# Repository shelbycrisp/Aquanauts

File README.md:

# Aquanauts
## Summary

The Exxon Valdez oil spill of 1989 is generally considered to have the largest environmental impact of any oil spill to date. Ocean Scientists at Prince William Sound have been using an underwater profiler to monitor environmental factors. The platform has an anchor that holds it at a specified depth. The platform goes to the surface of the water once a day to transmit a signal that it is still alive. The data collected on ocean life and ocean currents is not transmitted and must be retrieved by scientists. The collected data gives scientists information on how the location and its inhabitants are recovering. There are multiple ways this platform can be improved and updated. Currently, someone must retrieve the platform every few weeks in order to charge the battery and extract data. Over time the battery life has decreased, further increasing the maintenance required. If this maintenance could be decreased that would be a great improvement for the platform. Currently, it is very difficult and expensive to replace the battery. A battery that can be serviced by the scientists themselves would be ideal. The platform has many sensors on board to detect ocean life such as plankton. The current solution to classifying plankton is through the use of machine learning. However, there is room for improvement in this component. There is a weather buoy nearby that could potentially be used to install components on for communication with the platform. Our team is identifying which features/issues to focus our project on.

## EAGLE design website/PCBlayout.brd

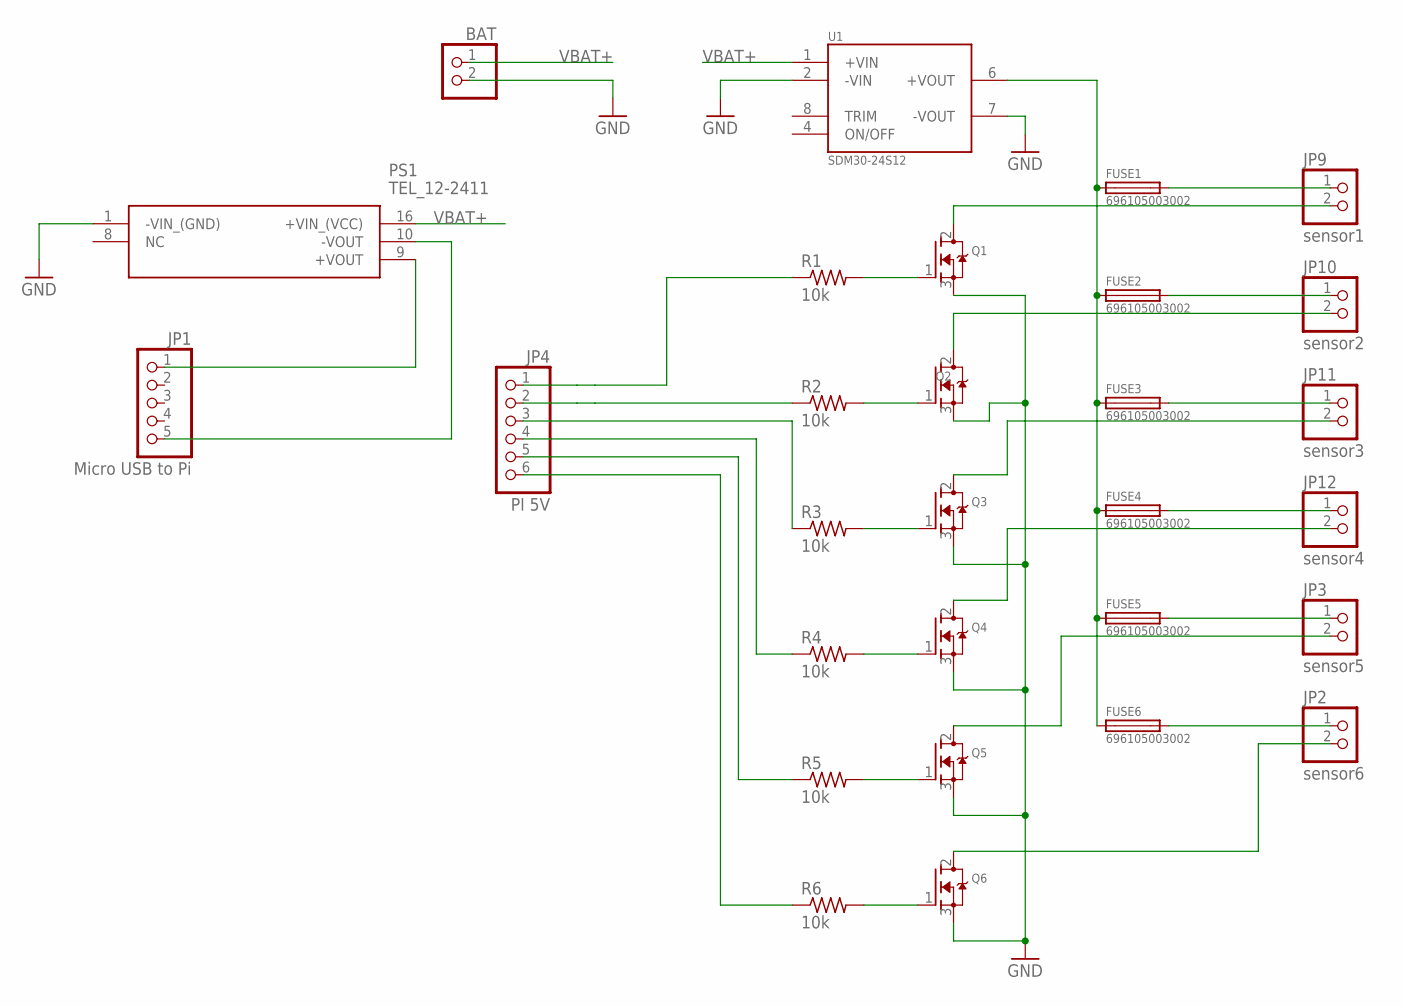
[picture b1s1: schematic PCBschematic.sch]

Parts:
BAT: PINHD-1X2; 1X02
FUSE1, FUSE2, FUSE3, FUSE4, FUSE5, FUSE6: 696105003002; FUSE_696105003002
JP1: Micro USB to Pi; 1X05
JP2: sensor6; 1X02
JP3: sensor5; 1X02
JP4: PI 5V; 1X06
JP9: sensor1; 1X02
JP10: sensor2; 1X02
JP11: sensor3; 1X02
JP12: sensor4; 1X02
PS1: TEL_12-2411; TEL122411
Q1, Q2, Q3, Q4, Q5, Q6: MOSFET-NGDS_TO220V; TO220V
R1, R2, R3, R4, R5, R6: 10k; M0805
U1: SDM30-24S12; CONV_SDM30-24S12

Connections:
GND: BAT.2, PS1.1 (-VIN_(GND)), Q1.3 (S), Q2.3 (S), Q3.3 (S), Q4.3 (S), Q5.3 (S), Q6.3 (S), U1.2 (-VIN), U1.7 (-VOUT)
unnamed: JP1.1, PS1.9 (+VOUT)
unnamed: JP1.5, PS1.10 (-VOUT)
unnamed: FUSE1.2, JP9.1
unnamed: FUSE2.2, JP10.1
unnamed: FUSE3.2, JP11.1
unnamed: FUSE4.2, JP12.1
unnamed: FUSE1.1, FUSE2.1, FUSE3.1, FUSE4.1, FUSE5.1, FUSE6.1, U1.6 (+VOUT)
unnamed: JP9.2, Q1.2 (D)
unnamed: JP10.2, Q2.2 (D)
unnamed: JP11.2, Q3.2 (D)
unnamed: JP12.2, Q4.2 (D)
unnamed: Q1.1 (G), R1.2
unnamed: Q2.1 (G), R2.2
unnamed: Q3.1 (G), R3.2
unnamed: Q4.1 (G), R4.2
unnamed: JP4.1, R1.1
unnamed: JP4.2, R2.1
unnamed: JP4.3, R3.1
unnamed: JP4.4, R4.1
unnamed: FUSE6.2, JP2.1
unnamed: JP2.2, Q6.2 (D)
unnamed: Q5.1 (G), R5.2
unnamed: Q6.1 (G), R6.2
unnamed: JP4.5, R5.1
unnamed: JP4.6, R6.1
unnamed: FUSE5.2, JP3.1
unnamed: JP3.2, Q5.2 (D)
VBAT+: BAT.1, PS1.16 (+VIN_(VCC)), U1.1 (+VIN)

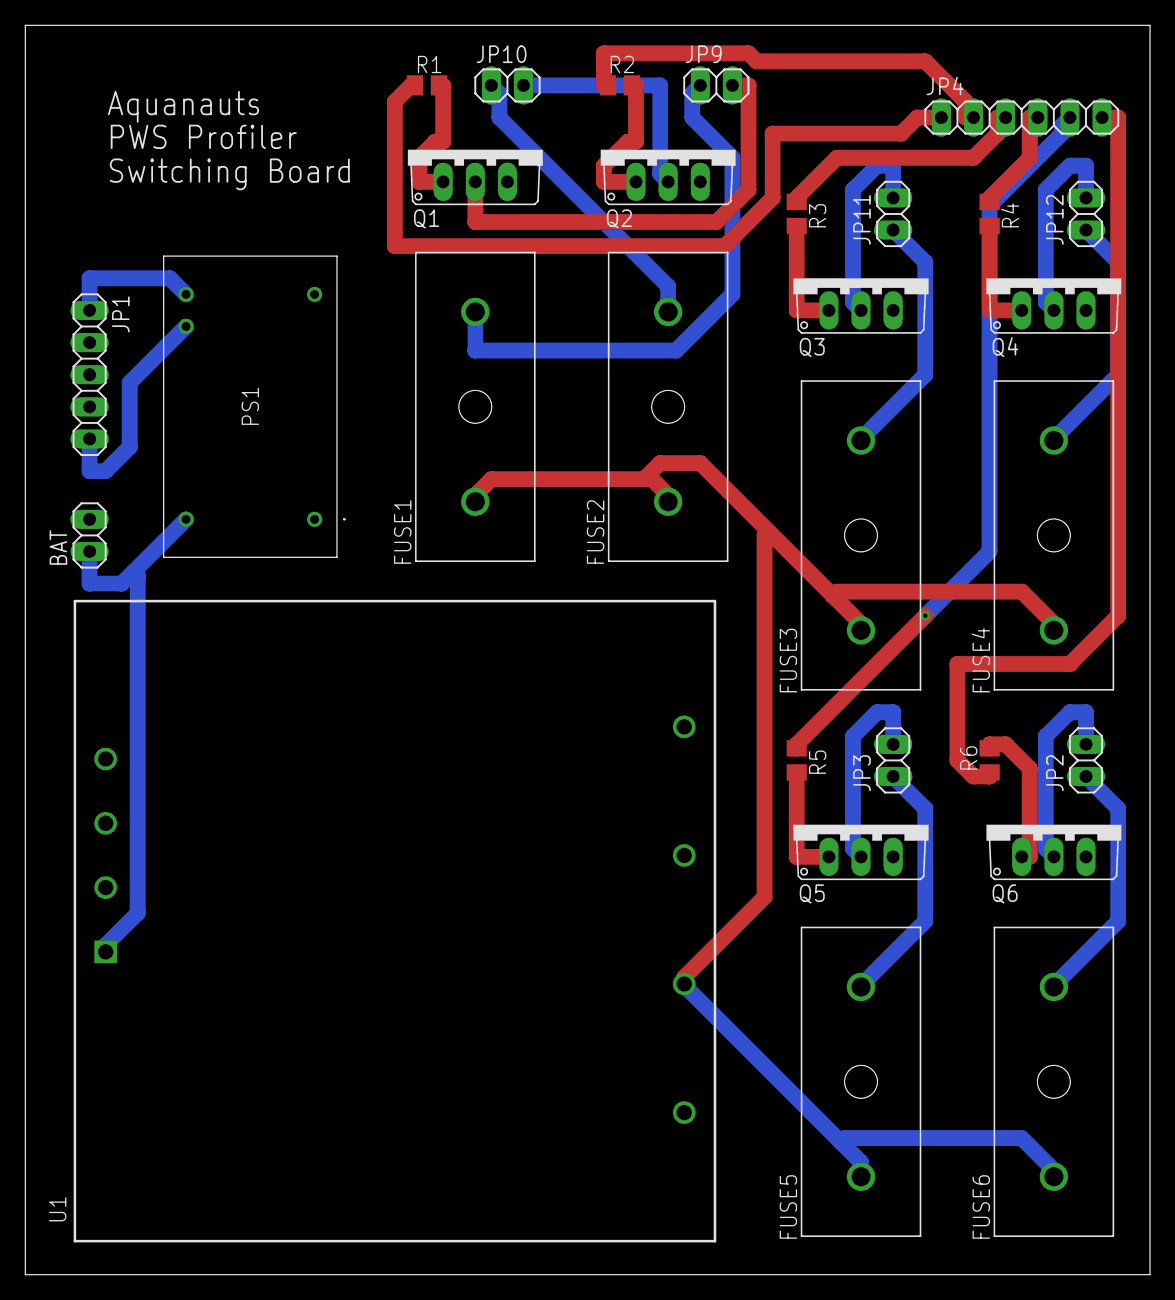
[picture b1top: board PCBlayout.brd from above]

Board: 2 copper layers, 88.9 x 98.7 mm, 29 parts (0 on the bottom side), 29 nets.

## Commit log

2021-04-08 First push of the Aquanauts website
2021-04-08 Removed photo that was no longer needed
2021-04-08 Added comms diagram, power diagram, and GitHub link to website under section called Additional Supporting Documentation
2021-04-09 Updated power diagram
2021-04-14 Added schematic and board files for the PCB
2021-04-21 Fixed the website header
2021-04-28 Added final presentation as of 4/28/21
2021-05-05 Added final report and manual
